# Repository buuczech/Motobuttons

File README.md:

# OsmAnd Moto Keypad (XIAO nRF52840)

A handlebar-mounted **Bluetooth LE HID keyboard** for controlling
[OsmAnd](https://osmand.net/) navigation on Android while riding. Built around
a Seeed Studio **XIAO nRF52840**, it exposes a small set of physical buttons as
HID keystrokes (zoom, pan, etc.), with key mappings that are **remappable over
BLE from a companion Android app** and firmware that updates **over-the-air
(OTA DFU)** — no cable, no removing the device from the bike.

> Status: active hobby project. Firmware and app evolve together.

\---

## Features

* **BLE HID keyboard** — pairs with Android as a standard keyboard; OsmAnd reacts
to the configured keys.
* **3 physical buttons**, each with **short / double / long** press, all sending
configurable HID keys.
* **Remote key remapping** — assign keys from the Android app over a BLE
characteristic; mappings persist in on-chip flash.
* **App-configurable settings** — e.g. `restartOnDisconnect` (auto re-advertise
after disconnect) is toggled from the app and persisted to flash.
* **OTA firmware updates** via the Adafruit nRF52 bootloader (Nordic DFU).
* **Soft-reset gesture** — hold both outer buttons for 3 s to cleanly reboot the
MCU, with an LED countdown.
* **Status LED** on an external pin with distinct states (advertising / connected
/ reset-arming / boot).
* **Compile-time TEST / PROD modes** — strip serial logging and debug LEDs from
production builds with a single flag.
* **Optional 5-way analog joystick** (voltage-divider on an ADC pin), behind a
compile flag so an unconnected, floating pin can't generate phantom presses.

\---

## Hardware

|Part|Notes|
|-|-|
|MCU|Seeed Studio XIAO nRF52840|
|Buttons|3 momentary, active-LOW, internal pull-ups (pins D0/D1/D2)|
|Status LED|External LED on D3 and/or D4 (active-HIGH in firmware)|
|Joystick (optional)|5-way, via voltage divider into an analog pin|
|Power|USB-C or 12V from the bike|

> The on-board RGB LED is not visible inside the enclosure on the target build,
> so the firmware drives an external LED. A `TEST\_MODE` build also mirrors status
> onto the built-in LED for bench testing.

\---

## Firmware

### Toolchain

* **Arduino IDE** (or arduino-cli) with **Seeed XIAO nRF52840** board support
(the Seeed nRF52 Boards package, based on the Adafruit nRF52 / Bluefruit core).
* The two custom libraries in `firmware/libraries/` (`MyBfButton`,
`MyBfButtonManager`) — modified from
[ButtonFever](https://github.com/mickey9801/ButtonFever) by Mickey Chan.

### Build / flash

1. Select board **Seeed XIAO nRF52840**.
2. Set the compile flags at the top of `osmand\_keypad.ino` (see below).
3. First flash via USB. Subsequent updates can go **OTA** (see *OTA updates*).

### Compile-time flags

|Flag|Default|Effect|
|-|-|-|
|`TEST\_MODE`|`1`|`1` = dev: serial console on, status mirrored to the built-in LED, BLE name `"Test Osmand Keyboard"`. `0` = production: no serial, no built-in LED, BLE name `"Osmand Keyboard"`.|
|`USE\_ANALOG`|`0`|`1` = read the 5-way joystick. `0` = analog code is compiled out entirely (safe when the joystick is not wired and the pin floats).|

Derived from `TEST\_MODE`: `ENABLE\_SERIAL` and `MIRROR\_BUILTIN\_LED`. All serial
output routes through `DBG\_\*` macros that expand to nothing in a production
build.

### Status LED states

|State|Pattern|
|-|-|
|Boot|three quick flashes (also confirms a reset completed)|
|Advertising / disconnected|slow \~500 ms blink|
|Connected|solid on|
|Reset arming|blink that accelerates over 3 s, then a rapid strobe before reboot|

### Soft-reset gesture

Hold **both outer buttons** (Dbtn1 + Dbtn3) for **3 s** → clean `NVIC\_SystemReset()`.
While the combo is held, normal key sending is suppressed so the gesture doesn't
emit stray keystrokes.

\---

## BLE protocol

Custom configuration service (alongside the standard HID, Device Information,
and DFU services):

* **Service UUID:** `12345678-1234-5678-1234-56789abcdef0`

### Key-mapping characteristic — `...def1` (Write, fixed 9 bytes)

Each button gets 3 bytes: `{ single, double, long }`. Values are **USB HID usage
IDs** (the `HID\_KEY\_\*` constants); `0x00` = no action.

> \*\*Important ordering gotcha.\*\* The firmware indexes the array as
> `customKeys\[getID() \* 3]`, and on this library `getID()` returns the \*\*pin
> number\*\*, not the construction order. The real byte → button mapping is:

|Bytes|Button|Pin|
|-|-|-|
|0–2|Dbtn3|0|
|3–5|Dbtn2|1|
|6–8|Dbtn1|2|

The Android app must send bytes in this order (`data\[0]` → Dbtn3).

### Settings characteristic — `...def2` (Write, fixed `SETTINGS\_LEN` bytes)

|Index|Setting|Values|
|-|-|-|
|0|`restartOnDisconnect`|`0x00` = false (default), `0x01` = true|

Writes are persisted to flash and applied live (no reboot needed). The length is
fixed, so when settings grow, bump `SETTINGS\_LEN` and update both sides together.

\---

## OTA updates

Firmware updates over BLE use the Adafruit nRF52 bootloader (Nordic legacy DFU).
The recommended Android path is the official
[Nordic Android DFU Library](https://github.com/NordicSemiconductor/Android-DFU-Library).

**Known issue — bonded GATT cache.** Because the device is an HID keyboard it is
bonded, and Android caches its services. The Adafruit bootloader keeps the same
MAC address in DFU mode, so the first OTA attempt can fail with
`GATT INVALID\_HANDLE` and succeed on retry. Practical mitigations (all app-side):

* `setNumberOfRetries(2..3)` on the `DfuServiceInitiator` (automates the retry
that already works).
* Keep the same address for legacy DFU (do **not** force-scan for `address+1`).
* Force a GATT cache refresh before connecting if needed.

See `docs/ble-protocol.md` and the project notes for details.

\---

## Android app

The companion app (in `android/`) handles:

* Pairing and connecting as the HID host.
* Reading/writing the key-mapping and settings characteristics.
* Triggering and running OTA DFU.

\---

## Credits \& license

* Firmware uses **Adafruit Bluefruit nRF52** (Adafruit / Nordic).
* `MyBfButton` / `MyBfButtonManager` are derived from **ButtonFever** by
Mickey Chan, MIT-licensed.

This project is released under the [MIT License](LICENSE) unless noted otherwise
in a subfolder. Third-party components keep their own licenses.

\---

*Built by BuuCzech Development.*

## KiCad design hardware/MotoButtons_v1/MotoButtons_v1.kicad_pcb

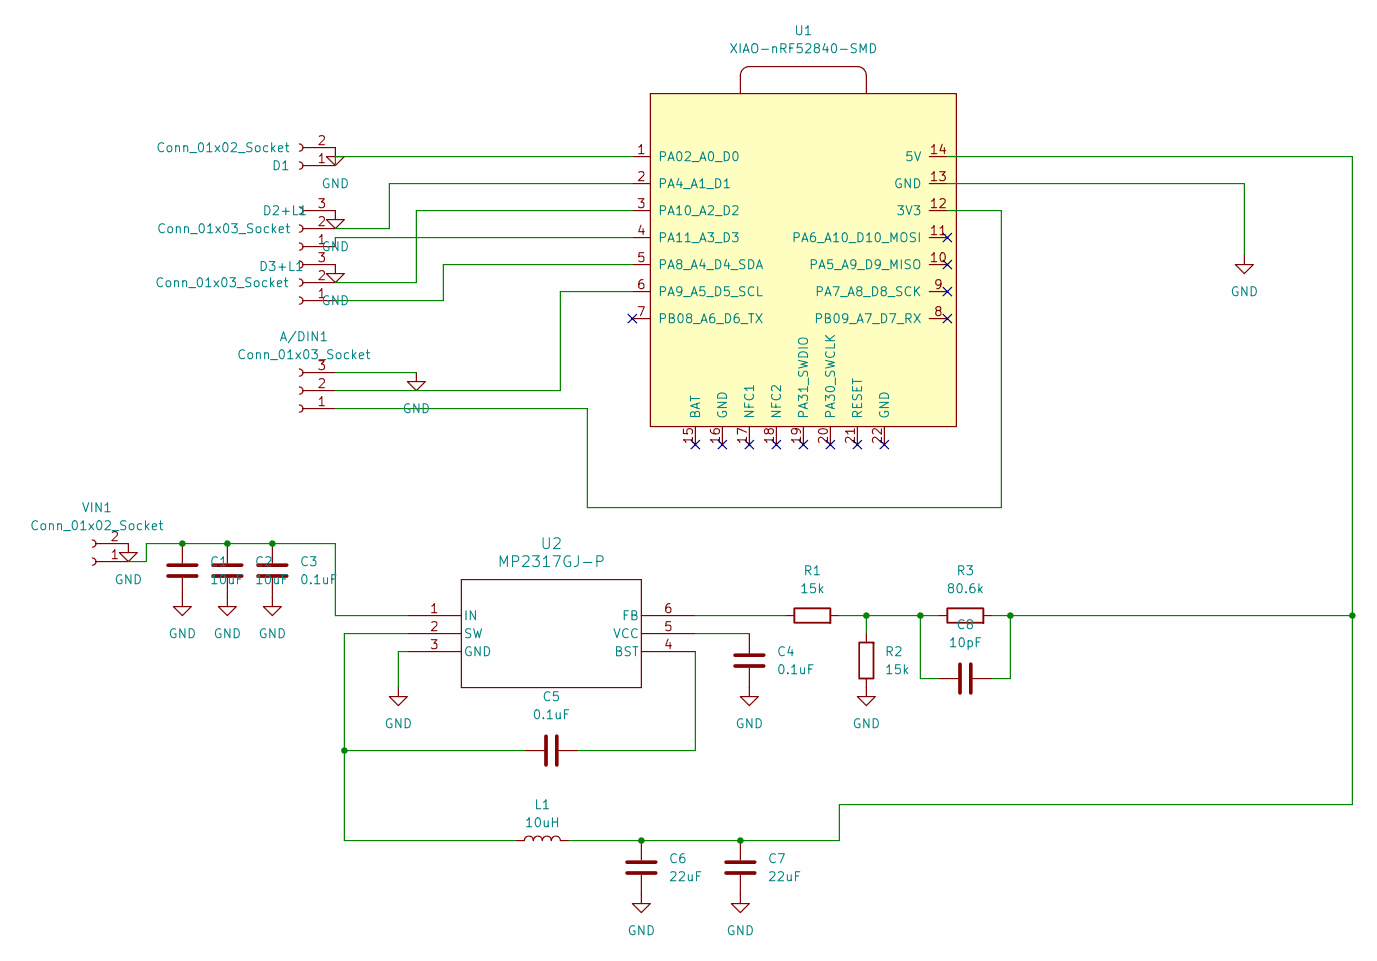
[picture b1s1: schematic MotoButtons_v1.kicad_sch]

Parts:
A/DIN1: Conn_01x03_Socket; Molex_SMD_3pin_2035560307
C1, C2: 10uF; C_0603_1608Metric_Pad1.08x0.95mm_HandSolder
C3, C4, C5: 0.1uF; C_0603_1608Metric_Pad1.08x0.95mm_HandSolder
C6, C7: 22uF; C_0603_1608Metric_Pad1.08x0.95mm_HandSolder
C8: 10pF; C_0603_1608Metric_Pad1.08x0.95mm_HandSolder
D1: Conn_01x02_Socket; Molex_SMD_2Pin_2035560207
D2+L1, D3+L1: Conn_01x03_Socket; Molex_SMD_3pin_2035560307
L1: 10uH; L_1008_2520Metric_Pad1.43x2.20mm_HandSolder
R1, R2: 15k; R_0603_1608Metric_Pad0.98x0.95mm_HandSolder
R3: 80.6k; R_0603_1608Metric_Pad0.98x0.95mm_HandSolder
U1: XIAO-nRF52840-SMD
U2: MP2317GJ-P; TSOT23-6_MPS_MNP
VIN1: Conn_01x02_Socket; JST_PH_B2B-PH-SM4-TB_1x02-1MP_P2.00mm_Vertical

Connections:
GND: A/DIN1.3, C1.2, C2.2, C3.2, C4.2, C6.2, C7.2, D1.2, D2+L1.3, D3+L1.3, R2.1, U1.13 (GND), U2.3 (GND), VIN1.2
unnamed: A/DIN1.1, U1.12 (3V3)
unnamed: A/DIN1.2, U1.6 (PA9_A5_D5_SCL)
unnamed: C8.1, R1.2, R2.2, R3.1
unnamed: D1.1, U1.1 (PA02_A0_D0)
unnamed: D2+L1.1, U1.4 (PA11_A3_D3)
unnamed: D2+L1.2, U1.2 (PA4_A1_D1)
unnamed: D3+L1.1, U1.5 (PA8_A4_D4_SDA)
unnamed: D3+L1.2, U1.3 (PA10_A2_D2)
unnamed: C6.1, C7.1, C8.2, L1.2, R3.2, U1.14 (5V)
unnamed: C5.1, U2.4 (BST)
unnamed: R1.1, U2.6 (FB)
unnamed: C1.1, C2.1, C3.1, U2.1 (IN), VIN1.1
unnamed: C5.2, L1.1, U2.2 (SW)
unnamed: C4.1, U2.5 (VCC)

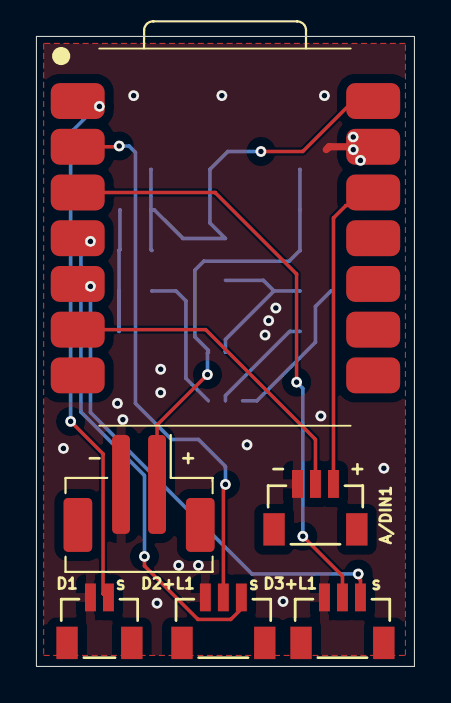
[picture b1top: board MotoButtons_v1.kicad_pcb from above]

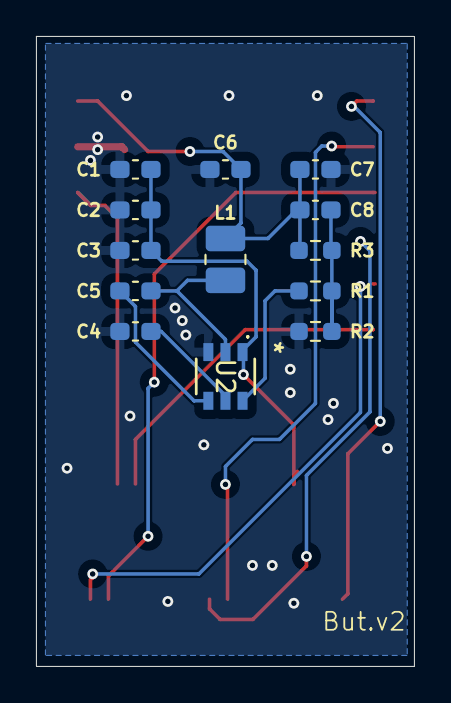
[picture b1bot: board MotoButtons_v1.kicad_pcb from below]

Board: 2 copper layers, 21.0 x 35.0 mm, 19 parts (13 on the bottom side), 15 nets.

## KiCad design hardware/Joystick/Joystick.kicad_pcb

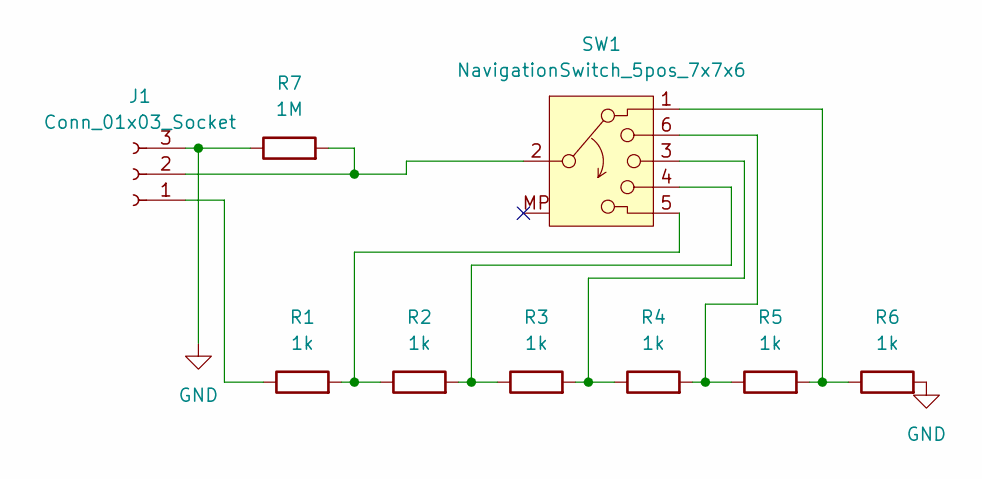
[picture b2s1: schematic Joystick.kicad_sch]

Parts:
J1: Conn_01x03_Socket; Molex_SMD_3pin_2035560307
R1, R2, R3, R4, R5, R6: 1k; R_0603_1608Metric_Pad0.98x0.95mm_HandSolder
R7: 1M; R_0603_1608Metric_Pad0.98x0.95mm_HandSolder
SW1: NavigationSwitch_5pos_7x7x6; Navigation Switch 7x7x6

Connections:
GND: J1.3, R6.2, R7.1
unnamed: J1.1, R1.1
unnamed: J1.2, R7.2, SW1.2
unnamed: R2.2, R3.1, SW1.4
unnamed: R3.2, R4.1, SW1.3
unnamed: R4.2, R5.1, SW1.6
unnamed: R5.2, R6.1, SW1.1
unnamed: R1.2, R2.1, SW1.5 (Push)

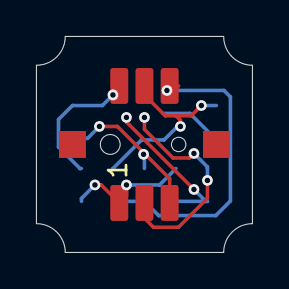
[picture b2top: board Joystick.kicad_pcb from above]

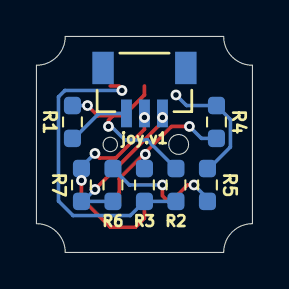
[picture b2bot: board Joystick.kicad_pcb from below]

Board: 2 copper layers, 12.0 x 12.0 mm, 9 parts (8 on the bottom side), 8 nets.

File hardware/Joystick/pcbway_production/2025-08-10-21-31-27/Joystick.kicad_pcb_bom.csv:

Designator,Quantity,Value,Footprint,Package,MPN,DNP,Mount_Type,Description
J1,1,Conn_01x03_Socket,Molex_SMD_3pin_2035560307,,,,smt,"Generic connector, single row, 01x03, script generated"
"R1, R2, R3, R4, R5, R6",6,1k,R_0603_1608Metric_Pad0.98x0.95mm_HandSolder,,,,smt,Resistor
R7,1,1M,R_0603_1608Metric_Pad0.98x0.95mm_HandSolder,,,,smt,Resistor
SW1,1,NavigationSwitch_5pos_7x7x6,Navigation Switch 7x7x6,,,,smt,"Rotary switch 1x5, SP5T with mount point"

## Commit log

2026-06-23 Initial commit
    Initial commit
2026-06-23 Folder Cleanup
2026-06-23 Apply .gitignore: stop tracking build artifacts and KiCad backups/caches
2026-06-23 Updateed Readme
2026-06-23 Stop tracking KiCad backup folders
2026-06-23 Stop tracking PCBWay production outputs
2026-06-23 added FW version info to the ino. Corrected .gitignore
2026-06-23 updated gitattributes
2026-06-23 corrected attributes
